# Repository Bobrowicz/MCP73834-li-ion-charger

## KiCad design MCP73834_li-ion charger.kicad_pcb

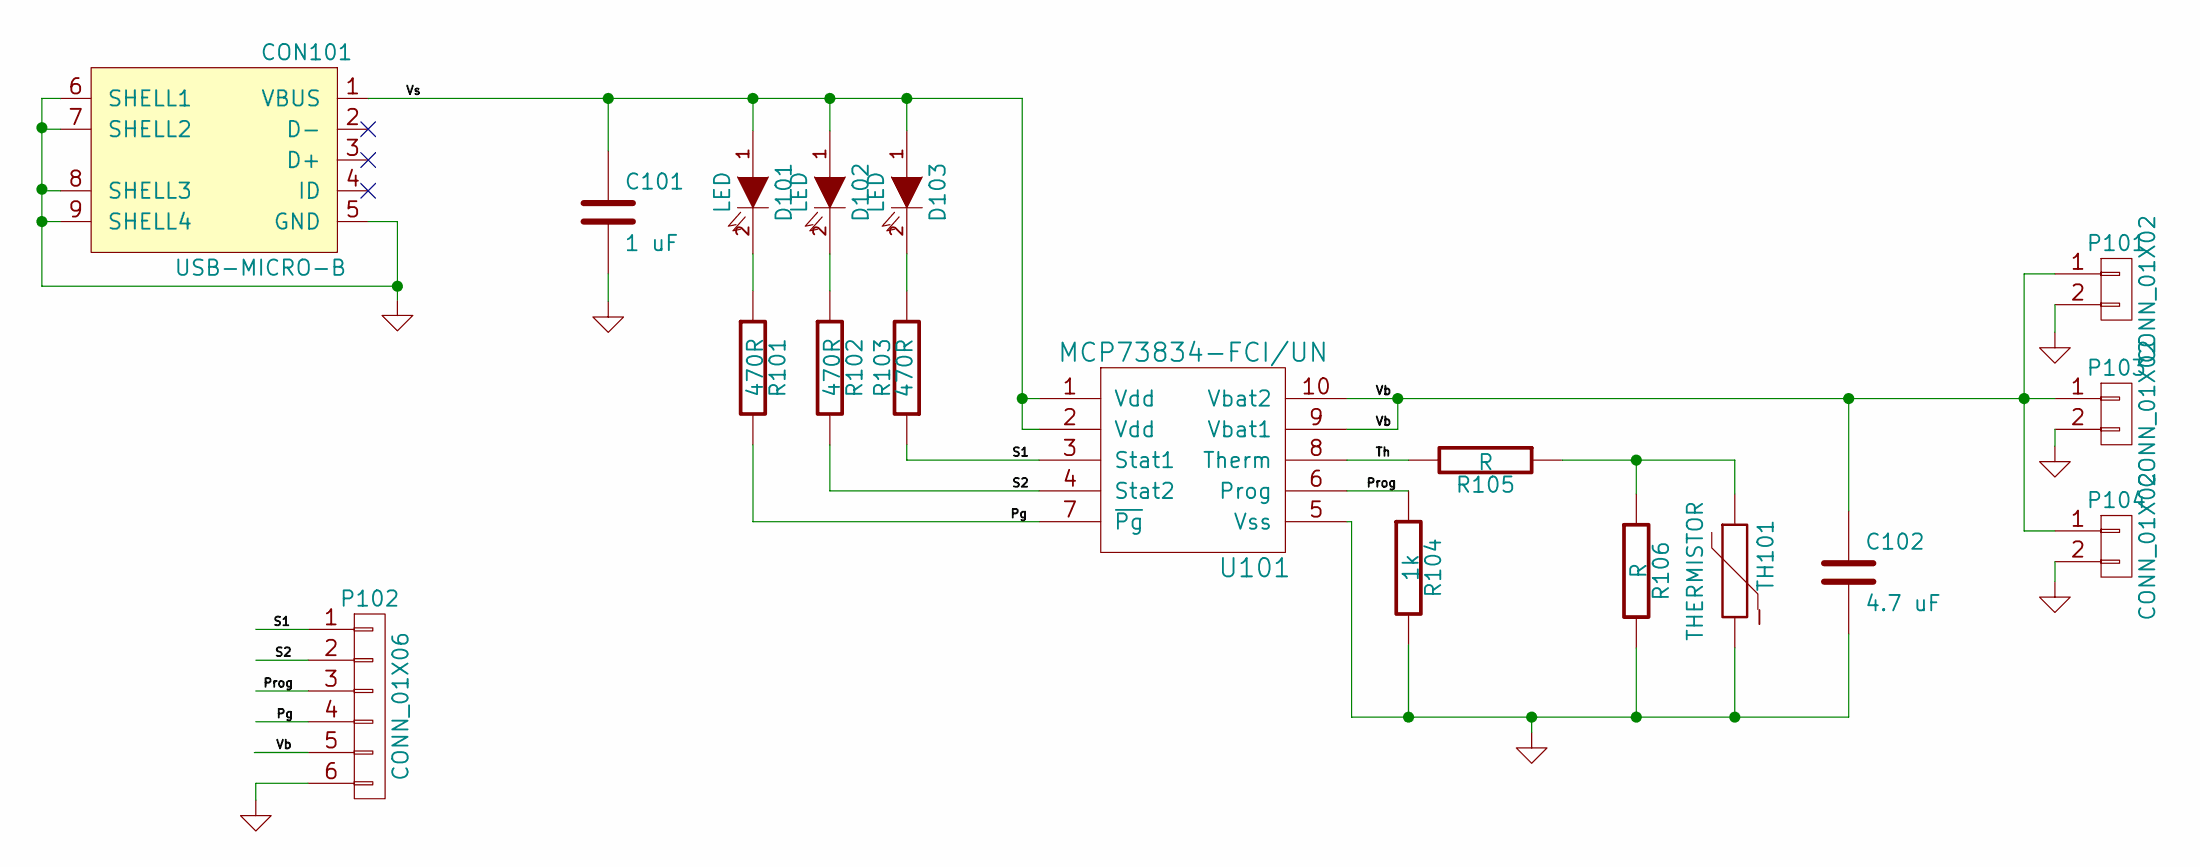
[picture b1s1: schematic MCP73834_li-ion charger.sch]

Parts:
C101: 1 uF; C_0805_HandSoldering
C102: 4.7 uF; C_0805_HandSoldering
CON101: USB-MICRO-B; USB_Micro-B_FCI_10118193-0001LF
D101, D102, D103: LED; LED-0805
P101, P104: CONN_01X02; Pin_Header_Straight_1x02
P102: CONN_01X06; Pin_Header_Straight_1x06
P103: CONN_01X02; Terminal_Block_1x2_3.5mm
R101, R102, R103: 470R; R_0805_HandSoldering
R104: 1k; R_0805_HandSoldering
R105, R106: R; R_0805_HandSoldering
TH101: THERMISTOR; Pin_Header_Straight_1x02
U101: MCP73834-FCI/UN

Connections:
/Pg: P102.4, R101.2, U101.7 (~Pg)
/Prog: P102.3, R104.1, U101.6 (Prog)
/S1: P102.1, R103.1, U101.3 (Stat1)
/S2: P102.2, R102.2, U101.4 (Stat2)
/Th: R105.2, U101.8 (Therm)
/Vb: C102.1, P101.1, P102.5, P103.1, P104.1, U101.9 (Vbat1), U101.10 (Vbat2)
/Vs: C101.1, CON101.1 (VBUS), D101.1 (A), D102.1 (A), D103.1 (A), U101.1 (Vdd), U101.2 (Vdd)
GND: C101.2, C102.2, CON101.5 (GND), CON101.6 (SHELL1), CON101.7 (SHELL2), CON101.8 (SHELL3), CON101.9 (SHELL4), P101.2, P102.6, P103.2, P104.2, R104.2, R106.2, TH101.2, U101.5 (Vss)
unnamed: D101.2 (K), R101.1
unnamed: D102.2 (K), R102.1
unnamed: D103.2 (K), R103.2
unnamed: R105.1, R106.1, TH101.1

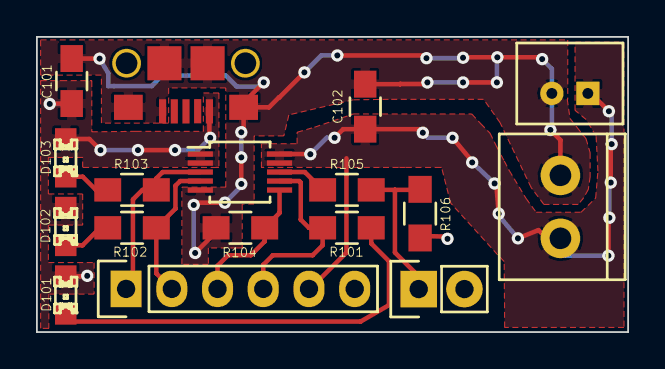
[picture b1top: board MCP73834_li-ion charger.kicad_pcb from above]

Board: 2 copper layers, 32.8 x 16.4 mm, 17 parts (0 on the bottom side), 12 nets.

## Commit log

2015-03-27 initial schematic
2015-03-27 associated components
2015-03-28 started layout
2015-03-29 finished layout
2015-04-02 changed layout
2015-04-03 generated gerber files
2015-04-05 assigned part numbers
